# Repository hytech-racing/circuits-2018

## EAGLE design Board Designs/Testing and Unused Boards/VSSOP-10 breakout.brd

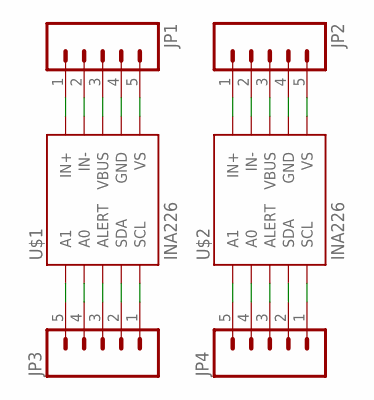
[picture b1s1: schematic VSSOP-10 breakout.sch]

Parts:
JP1, JP2, JP3, JP4: M05; 1X05
U$1, U$2: INA226; VSSOP-10

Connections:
unnamed: JP4.1, U$2.5 (SCL)
unnamed: JP4.2, U$2.4 (SDA)
unnamed: JP4.3, U$2.3 (ALERT)
unnamed: JP4.4, U$2.2 (A0)
unnamed: JP4.5, U$2.1 (A1)
unnamed: JP3.1, U$1.5 (SCL)
unnamed: JP3.2, U$1.4 (SDA)
unnamed: JP3.3, U$1.3 (ALERT)
unnamed: JP3.4, U$1.2 (A0)
unnamed: JP3.5, U$1.1 (A1)
unnamed: JP2.1, U$2.10 (IN+)
unnamed: JP2.2, U$2.9 (IN-)
unnamed: JP2.3, U$2.8 (VBUS)
unnamed: JP2.4, U$2.7 (GND)
unnamed: JP2.5, U$2.6 (VS)
unnamed: JP1.1, U$1.10 (IN+)
unnamed: JP1.2, U$1.9 (IN-)
unnamed: JP1.3, U$1.8 (VBUS)
unnamed: JP1.4, U$1.7 (GND)
unnamed: JP1.5, U$1.6 (VS)

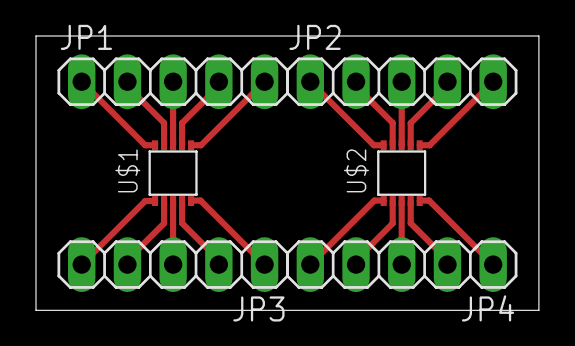
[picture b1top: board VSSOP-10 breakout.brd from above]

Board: 2 copper layers, 27.9 x 15.2 mm, 6 parts (0 on the bottom side), 20 nets.

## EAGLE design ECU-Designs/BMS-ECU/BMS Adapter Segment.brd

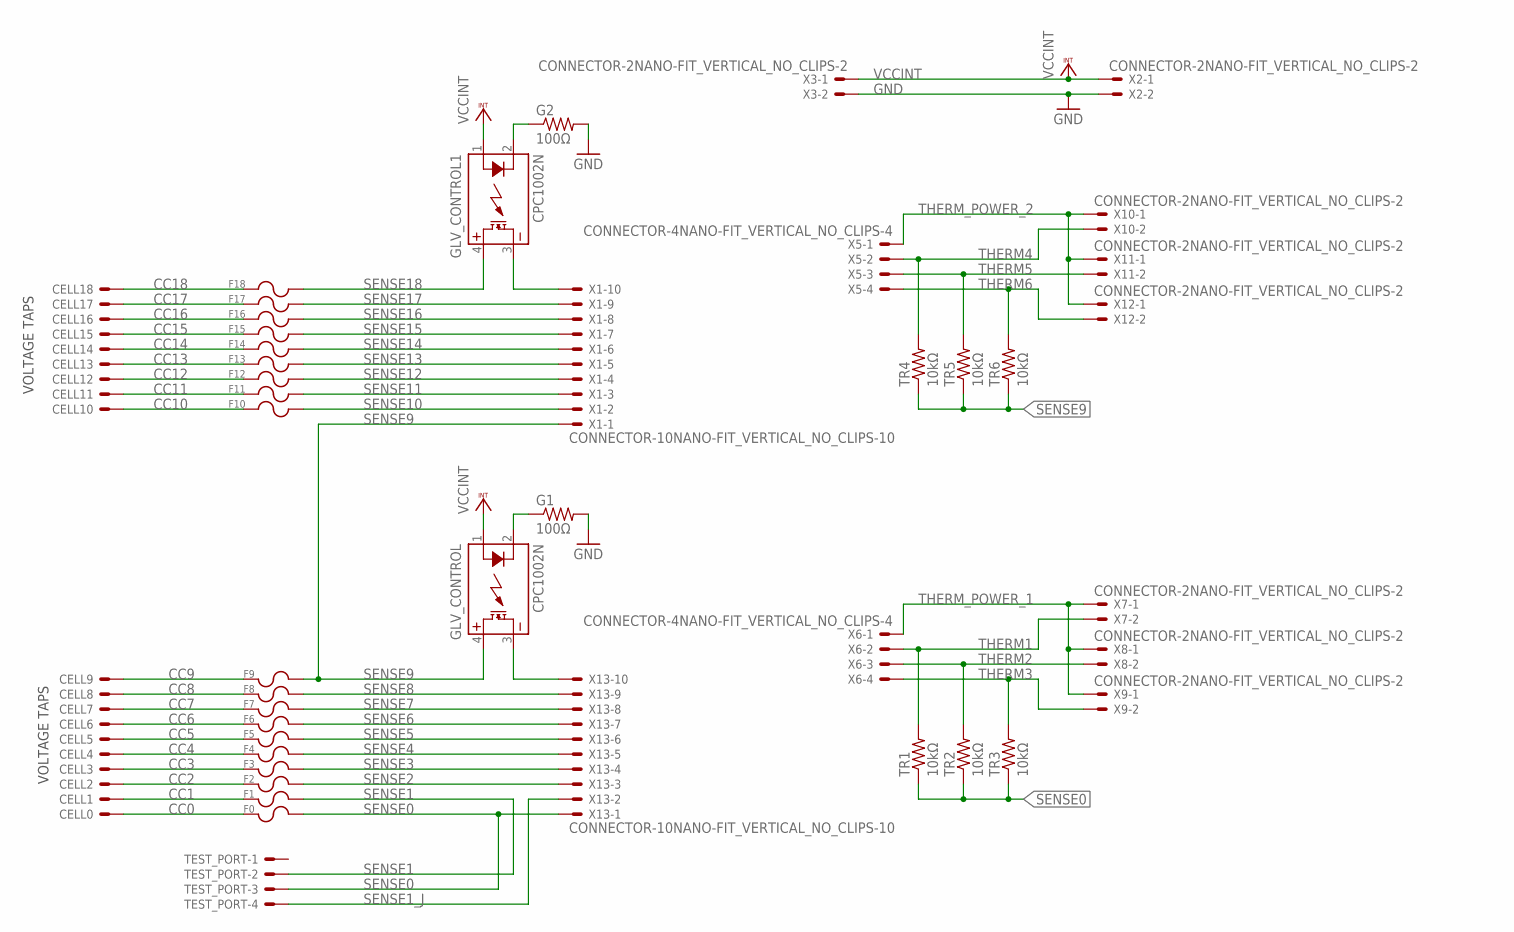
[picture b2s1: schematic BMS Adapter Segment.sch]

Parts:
CELL0, CELL1, CELL2, CELL3, CELL4, CELL5, CELL6, CELL7, CELL8, CELL9, CELL10, CELL11, CELL12, CELL13, CELL14, CELL15, CELL16, CELL17, CELL18: BATTERY_SPRING_KEYSTONE5222; KEYSTONE5222
F0, F1, F2, F3, F4, F5, F6, F7, F8, F9, F10, F11, F12, F13, F14, F15, F16, F17, F18: 0751.0110_FUSE_CLIP; 0751.0110
G1, G2: 100Ω; 0805
GLV_CONTROL, GLV_CONTROL1: CPC1002N; SOP04
TEST_PORT: MINIFIT_5566-4
TR1, TR2, TR3, TR4, TR5, TR6: 10kΩ; 0805
X1, X13: CONNECTOR-10NANO-FIT_VERTICAL_NO_CLIPS-10; NANO-FIT_VERTICAL_NO_CLIPS-10
X2, X3, X7, X8, X9, X10, X11, X12: CONNECTOR-2NANO-FIT_VERTICAL_NO_CLIPS-2; NANO-FIT_VERTICAL_NO_CLIPS-2
X5, X6: CONNECTOR-4NANO-FIT_VERTICAL_NO_CLIPS-4; NANO-FIT_VERTICAL_NO_CLIPS-4

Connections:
CC0: CELL0.P$1, F0.L1 (1), F0.L2 (1)
CC1: CELL1.P$1, F1.L1 (1), F1.L2 (1)
CC2: CELL2.P$1, F2.L1 (1), F2.L2 (1)
CC3: CELL3.P$1, F3.L1 (1), F3.L2 (1)
CC4: CELL4.P$1, F4.L1 (1), F4.L2 (1)
CC5: CELL5.P$1, F5.L1 (1), F5.L2 (1)
CC6: CELL6.P$1, F6.L1 (1), F6.L2 (1)
CC7: CELL7.P$1, F7.L1 (1), F7.L2 (1)
CC8: CELL8.P$1, F8.L1 (1), F8.L2 (1)
CC9: CELL9.P$1, F9.L1 (1), F9.L2 (1)
CC10: CELL10.P$1, F10.L1 (1), F10.L2 (1)
CC11: CELL11.P$1, F11.L1 (1), F11.L2 (1)
CC12: CELL12.P$1, F12.L1 (1), F12.L2 (1)
CC13: CELL13.P$1, F13.L1 (1), F13.L2 (1)
CC14: CELL14.P$1, F14.L1 (1), F14.L2 (1)
CC15: CELL15.P$1, F15.L1 (1), F15.L2 (1)
CC16: CELL16.P$1, F16.L1 (1), F16.L2 (1)
CC17: CELL17.P$1, F17.L1 (1), F17.L2 (1)
CC18: CELL18.P$1, F18.L1 (1), F18.L2 (1)
GND: G1.2, G2.2, X2.P$2, X3.P$2
unnamed: GLV_CONTROL1.3 (DC-), X1.P$10
unnamed: GLV_CONTROL.3 (DC-), X13.P$10
SENSE0: F0.R1 (2), F0.R2 (2), TEST_PORT.3, TR1.1, TR2.1, TR3.1, X13.P$1
SENSE1: F1.R1 (2), F1.R2 (2), TEST_PORT.2
SENSE1_J: TEST_PORT.4, X13.P$2
SENSE2: F2.R1 (2), F2.R2 (2), X13.P$3
SENSE3: F3.R1 (2), F3.R2 (2), X13.P$4
SENSE4: F4.R1 (2), F4.R2 (2), X13.P$5
SENSE5: F5.R1 (2), F5.R2 (2), X13.P$6
SENSE6: F6.R1 (2), F6.R2 (2), X13.P$7
SENSE7: F7.R1 (2), F7.R2 (2), X13.P$8
SENSE8: F8.R1 (2), F8.R2 (2), X13.P$9
SENSE9: F9.R1 (2), F9.R2 (2), GLV_CONTROL.4 (DC+), TR4.1, TR5.1, TR6.1, X1.P$1
SENSE10: F10.R1 (2), F10.R2 (2), X1.P$2
SENSE11: F11.R1 (2), F11.R2 (2), X1.P$3
SENSE12: F12.R1 (2), F12.R2 (2), X1.P$4
SENSE13: F13.R1 (2), F13.R2 (2), X1.P$5
SENSE14: F14.R1 (2), F14.R2 (2), X1.P$6
SENSE15: F15.R1 (2), F15.R2 (2), X1.P$7
SENSE16: F16.R1 (2), F16.R2 (2), X1.P$8
SENSE17: F17.R1 (2), F17.R2 (2), X1.P$9
SENSE18: F18.R1 (2), F18.R2 (2), GLV_CONTROL1.4 (DC+)
SSR-: G1.1, GLV_CONTROL.2 (CONTROL-)
SSR-1: G2.1, GLV_CONTROL1.2 (CONTROL-)
THERM1: TR1.2, X6.P$2, X7.P$2
THERM2: TR2.2, X6.P$3, X8.P$2
THERM3: TR3.2, X6.P$4, X9.P$2
THERM4: TR4.2, X5.P$2, X10.P$2
THERM5: TR5.2, X5.P$3, X11.P$2
THERM6: TR6.2, X5.P$4, X12.P$2
THERM_POWER_1: X6.P$1, X7.P$1, X8.P$1, X9.P$1
THERM_POWER_2: X5.P$1, X10.P$1, X11.P$1, X12.P$1
VCCINT: GLV_CONTROL.1 (CONTROL+), GLV_CONTROL1.1 (CONTROL+), X2.P$1, X3.P$1

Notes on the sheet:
VOLTAGE TAPS

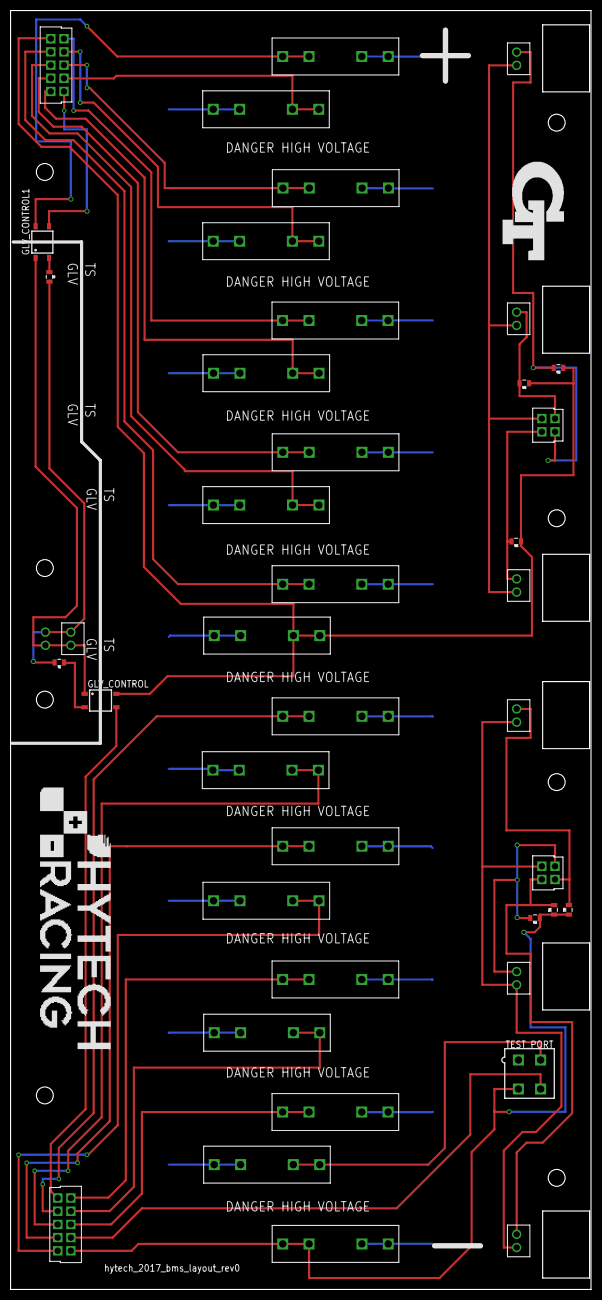
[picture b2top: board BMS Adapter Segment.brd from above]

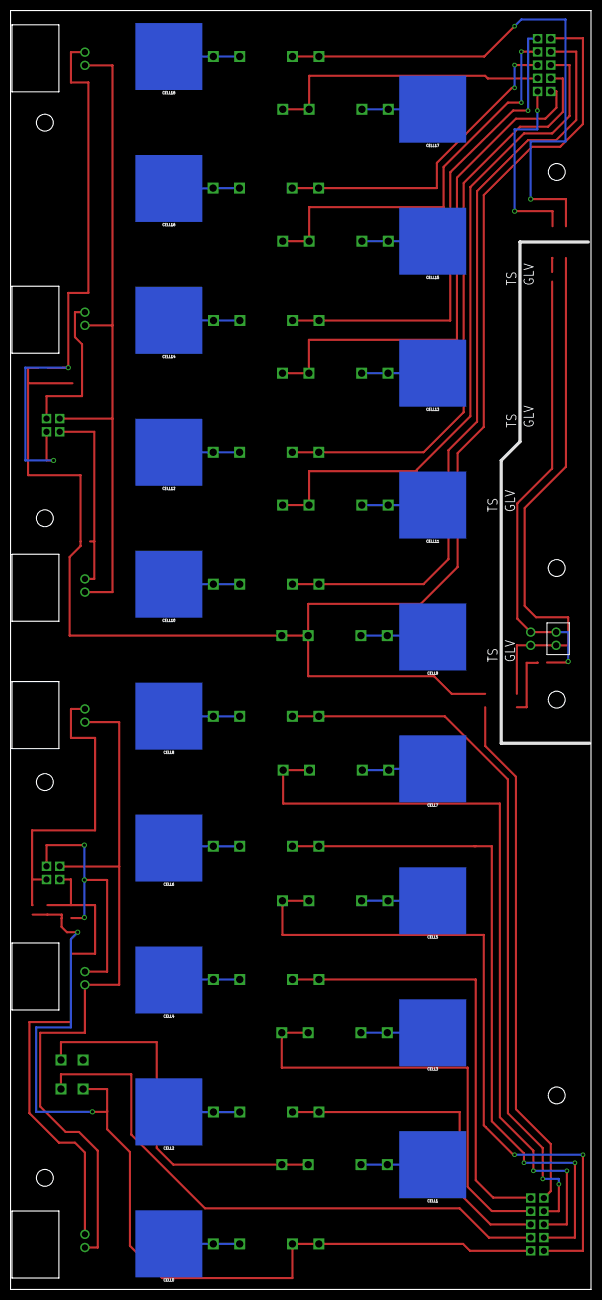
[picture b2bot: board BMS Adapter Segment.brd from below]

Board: 2 copper layers, 110.0 x 242.4 mm, 61 parts (20 on the bottom side), 53 nets.

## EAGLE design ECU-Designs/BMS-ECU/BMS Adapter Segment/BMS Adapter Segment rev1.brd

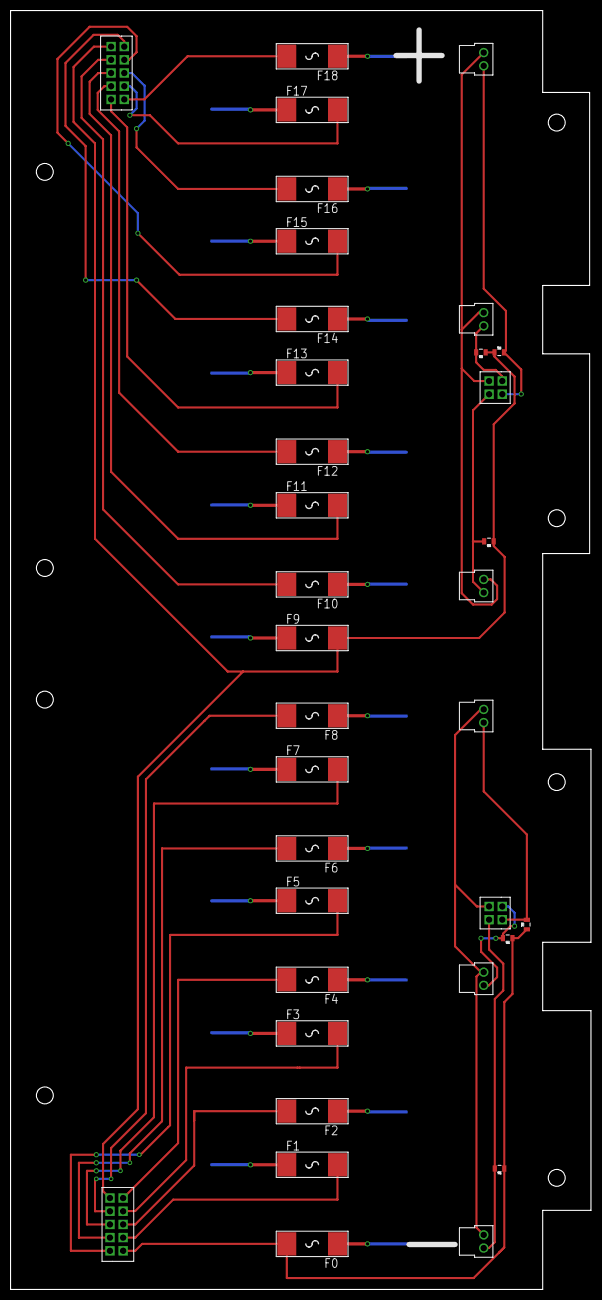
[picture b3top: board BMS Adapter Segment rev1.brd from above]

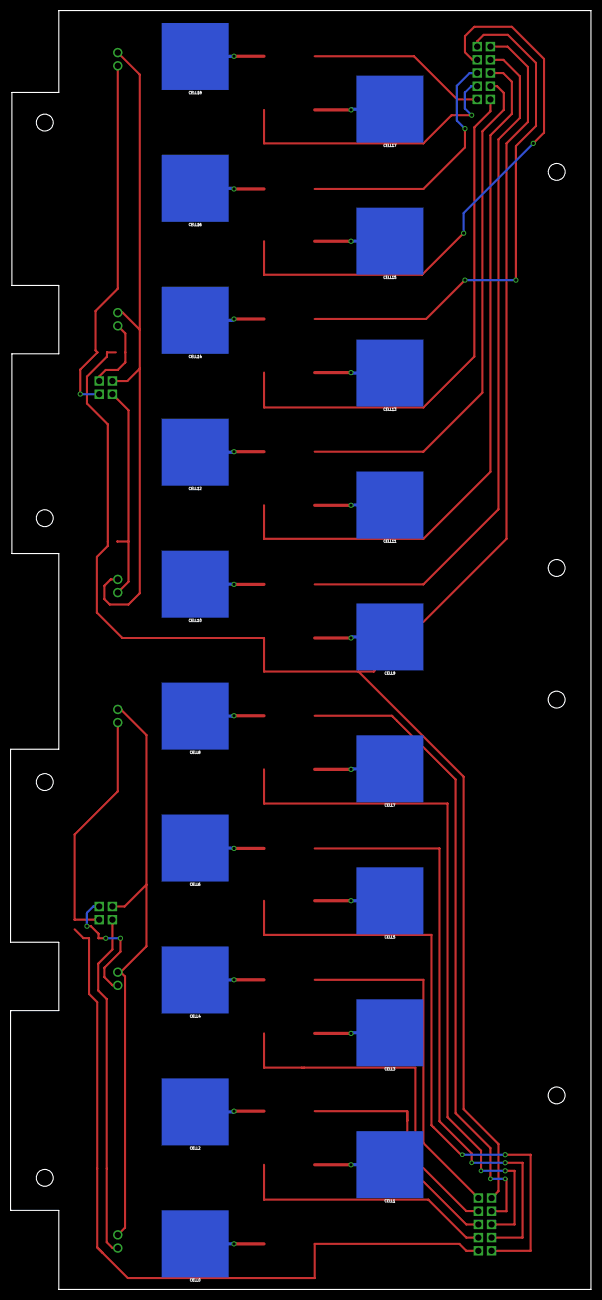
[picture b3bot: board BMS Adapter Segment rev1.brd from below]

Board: 2 copper layers, 110.0 x 242.3 mm, 54 parts (19 on the bottom side), 46 nets.

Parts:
CELL0, CELL1, CELL2, CELL3, CELL4, CELL5, CELL6, CELL7, CELL8, CELL9, CELL10, CELL11, CELL12, CELL13, CELL14, CELL15, CELL16, CELL17, CELL18: KEYSTONE5222
F0, F1, F2, F3, F4, F5, F6, F7, F8, F9, F10, F11, F12, F13, F14, F15, F16, F17, F18: OMF_250
TR1, TR2, TR3, TR4, TR5, TR6: 10kΩ; 0805
X1, X13: CONNECTOR-10NANO-FIT_VERTICAL-10; NANO-FIT_VERTICAL-10
X5, X6: CONNECTOR-4NANO-FIT-VERTICAL-4; NANO-FIT_VERTICAL-4
X7, X8, X9, X10, X11, X12: CONNECTOR-2NANO-FIT_VERTICAL-2; NANO-FIT_VERTICAL-2

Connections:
CC0: CELL0.P$1, F0.P$1
CC1: CELL1.P$1, F1.P$1
CC2: CELL2.P$1, F2.P$1
CC3: CELL3.P$1, F3.P$1
CC4: CELL4.P$1, F4.P$1
CC5: CELL5.P$1, F5.P$1
CC6: CELL6.P$1, F6.P$1
CC7: CELL7.P$1, F7.P$1
CC8: CELL8.P$1, F8.P$1
CC9: CELL9.P$1, F9.P$1
CC10: CELL10.P$1, F10.P$1
CC11: CELL11.P$1, F11.P$1
CC12: CELL12.P$1, F12.P$1
CC13: CELL13.P$1, F13.P$1
CC14: CELL14.P$1, F14.P$1
CC15: CELL15.P$1, F15.P$1
CC16: CELL16.P$1, F16.P$1
CC17: CELL17.P$1, F17.P$1
CC18: CELL18.P$1, F18.P$1
SENSE0: F0.P$2, TR1.1, TR2.1, TR3.1, X13.P$1
SENSE1: F1.P$2, X13.P$2
SENSE2: F2.P$2, X13.P$3
SENSE3: F3.P$2, X13.P$4
SENSE4: F4.P$2, X13.P$5
SENSE5: F5.P$2, X13.P$6
SENSE6: F6.P$2, X13.P$7
SENSE7: F7.P$2, X13.P$8
SENSE8: F8.P$2, X13.P$9
SENSE9: F9.P$2, TR4.1, TR5.1, TR6.1, X1.P$1, X13.P$10
SENSE10: F10.P$2, X1.P$2
SENSE11: F11.P$2, X1.P$3
SENSE12: F12.P$2, X1.P$4
SENSE13: F13.P$2, X1.P$5
SENSE14: F14.P$2, X1.P$6
SENSE15: F15.P$2, X1.P$7
SENSE16: F16.P$2, X1.P$8
SENSE17: F17.P$2, X1.P$9
SENSE18: F18.P$2, X1.P$10
THERM1: TR1.2, X6.P$2, X7.P$2
THERM2: TR2.2, X6.P$3, X8.P$2
THERM3: TR3.2, X6.P$4, X9.P$2
THERM4: TR4.2, X5.P$2, X10.P$2
THERM5: TR5.2, X5.P$3, X11.P$2
THERM6: TR6.2, X5.P$4, X12.P$2
THERM_POWER_1: X6.P$1, X7.P$1, X8.P$1, X9.P$1
THERM_POWER_2: X5.P$1, X10.P$1, X11.P$1, X12.P$1

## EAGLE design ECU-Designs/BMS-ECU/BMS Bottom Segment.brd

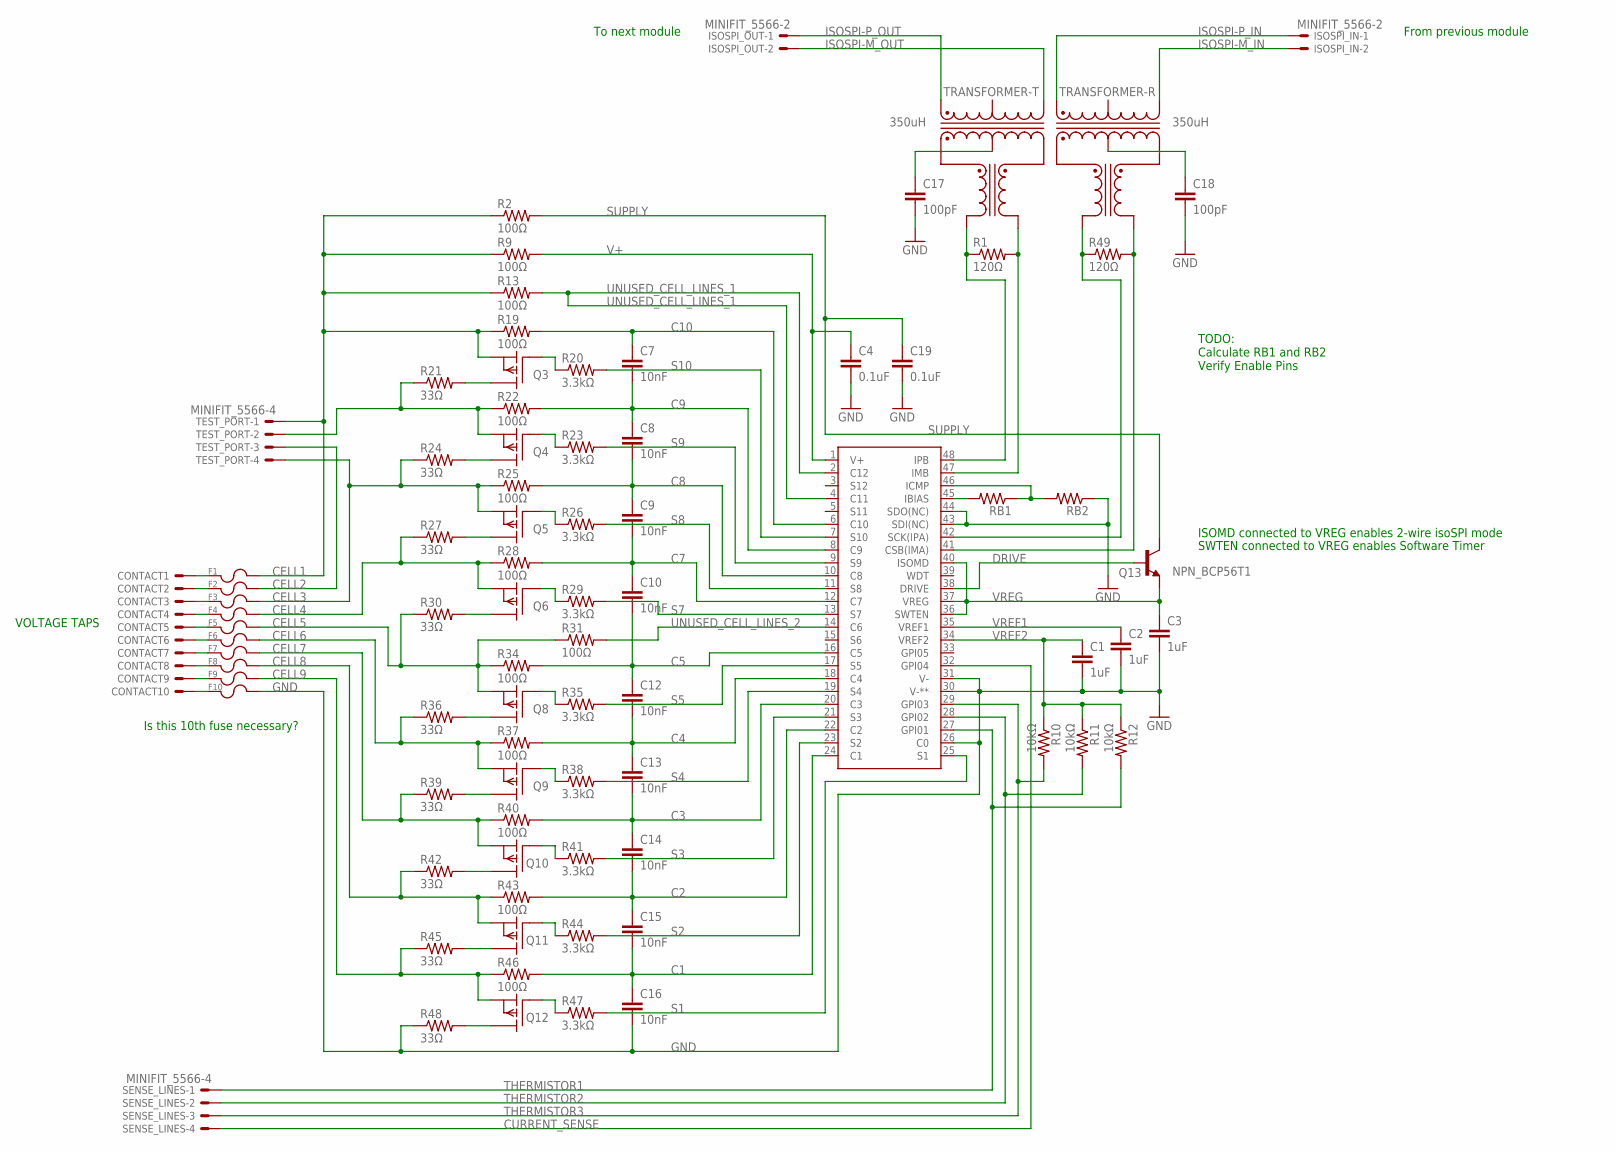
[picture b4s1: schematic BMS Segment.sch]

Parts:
C1, C2, C3: 1uF; 0805
C4, C19: 0.1uF; 0805
C7, C8, C9, C10, C12, C13, C14, C15, C16: 10nF; 0805
C17, C18: 100pF; 0805
CONTACT1, CONTACT2, CONTACT3, CONTACT4, CONTACT5, CONTACT6, CONTACT7, CONTACT8, CONTACT9, CONTACT10: SPRING_CONTACT; S1791-42R
F1, F2, F3, F4, F5, F6, F7, F8, F9, F10: 0751.0110_FUSE_CLIP; 0751.0110
ISOSPI_IN: MINIFIT_5566-2
ISOSPI_OUT: MINIFIT_5566-2
Q3, Q4, Q5, Q6, Q8, Q9, Q10, Q11, Q12: P-CHANNEL_MOSFET_DMP3099L-7; SOT23
Q13: NPN_BCP56T1; SOT223
R1, R49: 120Ω; 0805
R2, R9, R13, R19, R22, R25, R28, R31, R34, R37, R40, R43, R46: 100Ω; 0805
R10, R11, R12: 10kΩ; 0805
R20, R23, R26, R29, R35, R38, R41, R44, R47: 3.3kΩ; 0805
R21, R24, R27, R30, R36, R39, R42, R45, R48: 33Ω; R2512
RB1, RB2: RESISTOR0805-RES; 0805
SENSE_LINES: MINIFIT_5566-4
TEST_PORT: MINIFIT_5566-4
TRANSFORMER-: 350uH; 749010013
U$2: LTC6804-1; LTC6804

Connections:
C1: C15.2, C16.1, R46.2, U$2.24 (C1)
C2: C14.2, C15.1, R43.2, U$2.22 (C2)
C3: C13.2, C14.1, R40.2, U$2.20 (C3)
C4: C12.2, C13.1, R37.2, U$2.18 (C4)
C5: C10.2, C12.1, R34.2, U$2.16 (C5)
C7: C9.2, C10.1, R28.2, U$2.12 (C7)
C8: C8.2, C9.1, R25.2, U$2.10 (C8)
C9: C7.2, C8.1, R22.2, U$2.8 (C9)
C10: C7.1, R19.2, U$2.6 (C10)
CELL1: F1.R1 (2), F1.R2 (2), Q3.2 (S), R2.1, R9.1, R13.1, R19.1, TEST_PORT.1
CELL2: F2.R1 (2), F2.R2 (2), Q4.2 (S), R21.1, R22.1, TEST_PORT.2, TEST_PORT.3
CELL3: F3.R1 (2), F3.R2 (2), Q5.2 (S), R24.1, R25.1, TEST_PORT.4
CELL4: F4.R1 (2), F4.R2 (2), Q6.2 (S), R27.1, R28.1
CELL5: F5.R1 (2), F5.R2 (2), Q8.2 (S), R30.1, R31.1, R34.1
CELL6: F6.R1 (2), F6.R2 (2), Q9.2 (S), R36.1, R37.1
CELL7: F7.R1 (2), F7.R2 (2), Q10.2 (S), R39.1, R40.1
CELL8: F8.R1 (2), F8.R2 (2), Q11.2 (S), R42.1, R43.1
CELL9: F9.R1 (2), F9.R2 (2), Q12.2 (S), R45.1, R46.1
CURRENT_SENSE: SENSE_LINES.4, U$2.32 (GPI04)
DRIVE: Q13.1 (BASE), U$2.38 (DRIVE)
GND: C1.2, C2.2, C3.2, C4.2, C16.2, C17.2, C18.2, C19.2, F10.R1 (2), F10.R2 (2), R48.1, RB2.1, U$2.26 (C0), U$2.30 (V-**), U$2.31 (V-), U$2.43 (SDI(NC)), U$2.44 (SDO(NC))
unnamed: C18.1, TRANSFORMER-.10 (CX)
unnamed: C17.1, TRANSFORMER-.15 (CX)
unnamed: RB1.2, U$2.45 (IBIAS)
unnamed: R1.1, TRANSFORMER-.16 (X+), U$2.48 (IPB)
unnamed: RB1.1, RB2.2, U$2.46 (ICMP)
unnamed: R49.1, TRANSFORMER-.11 (X+), U$2.42 (SCK(IPA))
unnamed: R49.2, TRANSFORMER-.9 (X-), U$2.41 (CSB(IMA))
unnamed: CONTACT1.P$1, F1.L1 (1), F1.L2 (1)
unnamed: Q3.1 (G), R20.1
unnamed: CONTACT2.P$1, F2.L1 (1), F2.L2 (1)
unnamed: CONTACT3.P$1, F3.L1 (1), F3.L2 (1)
unnamed: Q3.3 (D), R21.2
unnamed: CONTACT4.P$1, F4.L1 (1), F4.L2 (1)
unnamed: Q8.1 (G), R35.1
unnamed: Q9.1 (G), R38.1
unnamed: CONTACT5.P$1, F5.L1 (1), F5.L2 (1)
unnamed: CONTACT6.P$1, F6.L1 (1), F6.L2 (1)
unnamed: Q4.3 (D), R24.2
unnamed: CONTACT7.P$1, F7.L1 (1), F7.L2 (1)
unnamed: Q10.1 (G), R41.1
unnamed: Q11.1 (G), R44.1
unnamed: Q12.1 (G), R47.1
unnamed: Q5.3 (D), R27.2
unnamed: CONTACT8.P$1, F8.L1 (1), F8.L2 (1)
unnamed: CONTACT9.P$1, F9.L1 (1), F9.L2 (1)
unnamed: CONTACT10.P$1, F10.L1 (1), F10.L2 (1)
unnamed: Q6.3 (D), R30.2
unnamed: R1.2, TRANSFORMER-.14 (X-), U$2.47 (IMB)
unnamed: Q8.3 (D), R36.2
unnamed: Q9.3 (D), R39.2
unnamed: Q10.3 (D), R42.2
unnamed: Q11.3 (D), R45.2
unnamed: Q12.3 (D), R48.2
unnamed: Q4.1 (G), R23.1
unnamed: Q5.1 (G), R26.1
unnamed: Q6.1 (G), R29.1
S1: R47.2, U$2.25 (S1)
S2: R44.2, U$2.23 (S2)
S3: R41.2, U$2.21 (S3)
S4: R38.2, U$2.19 (S4)
S5: R35.2, U$2.17 (S5)
S7: R29.2, U$2.13 (S7)
S8: R26.2, U$2.11 (S8)
S9: R23.2, U$2.9 (S9)
S10: R20.2, U$2.7 (S10)
SUPPLY: C19.1, Q13.2 (COLLECTOR), Q13.4 (COLLECTOR), R2.2
THERMISTOR1: R12.2, SENSE_LINES.1, U$2.27 (GPI01)
THERMISTOR2: R11.2, SENSE_LINES.2, U$2.28 (GPI02)
THERMISTOR3: R10.2, SENSE_LINES.3, U$2.29 (GPI03)
UNUSED_CELL_LINES_1: R13.2, U$2.2 (C12), U$2.4 (C11)
UNUSED_CELL_LINES_2: R31.2, U$2.14 (C6)
V+: C4.1, R9.2, U$2.1 (V+)
VREF1: C2.1, U$2.35 (VREF1)
VREF2: C1.1, R10.1, R11.1, R12.1, U$2.34 (VREF2)
VREG: C3.1, Q13.3 (EMITTER), U$2.36 (SWTEN), U$2.37 (VREG), U$2.40 (ISOMD)

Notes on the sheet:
SWTEN connected to VREG enables Software Timer
ISOMD connected to VREG enables 2-wire isoSPI mode
VOLTAGE TAPS
To next module
From previous module
TODO: Calculate RB1 and RB2 Verify Enable Pins
Is this 10th fuse necessary?

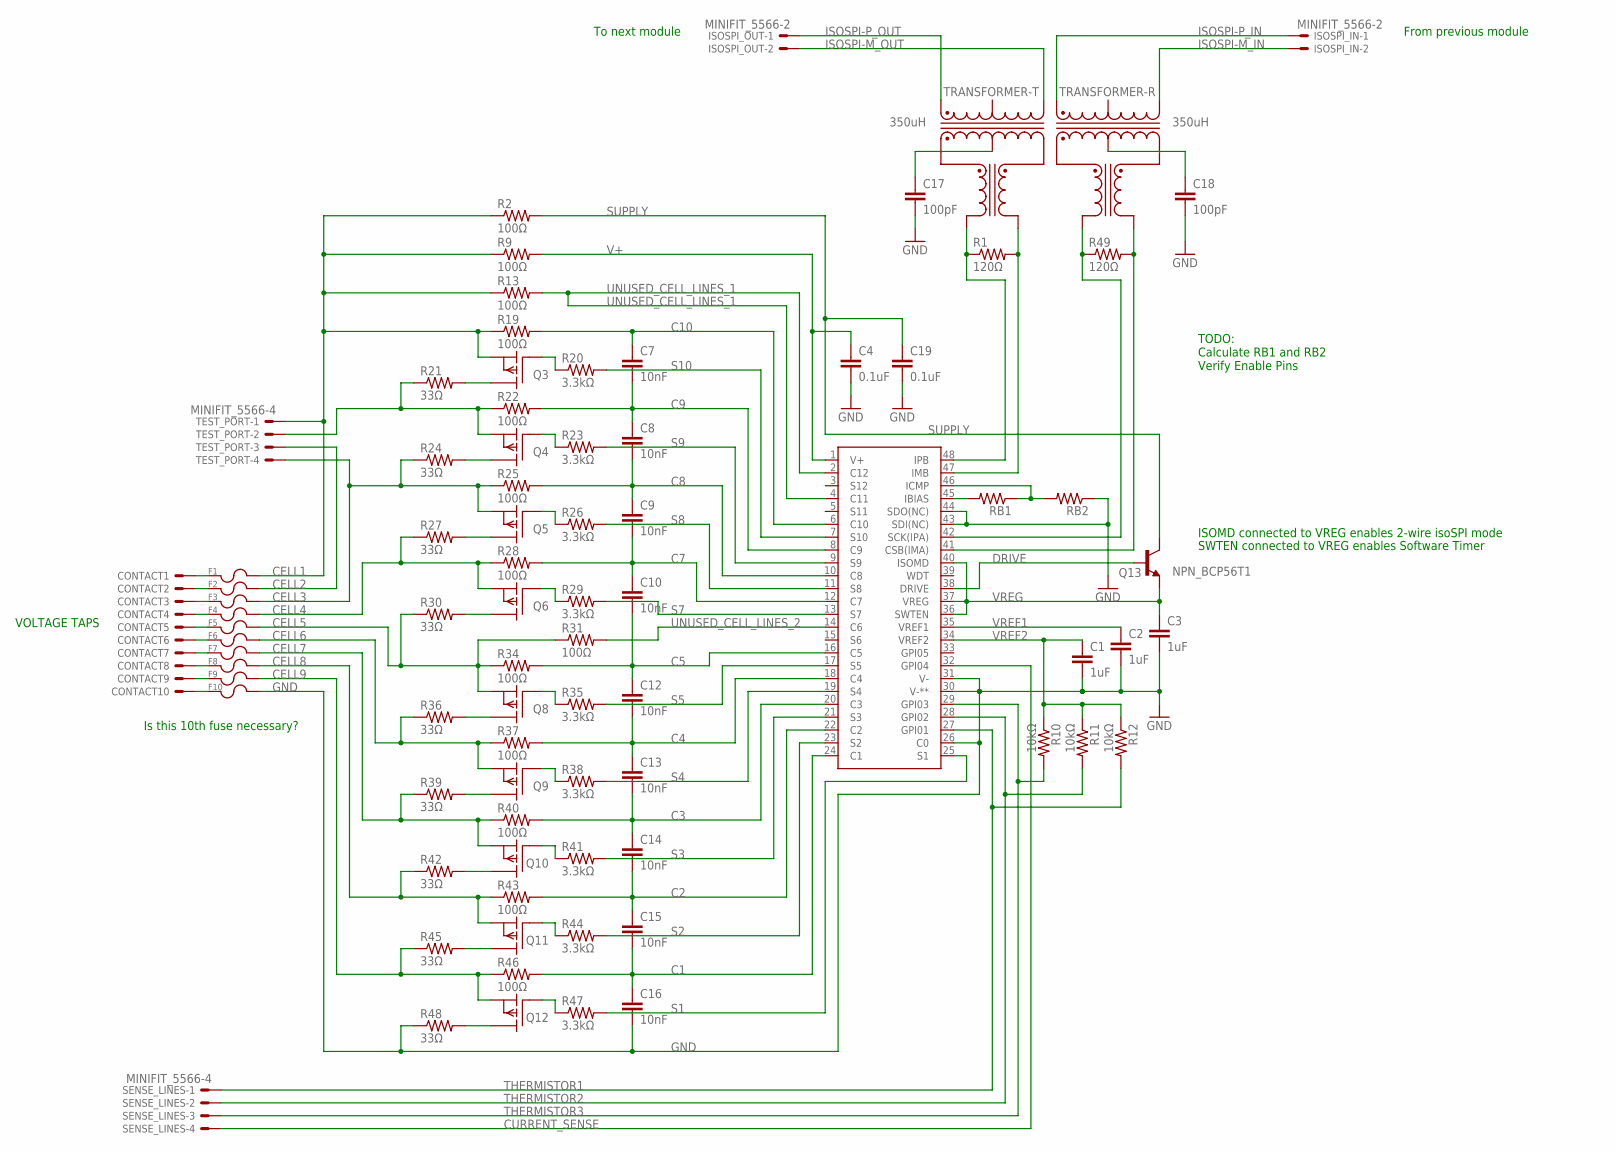
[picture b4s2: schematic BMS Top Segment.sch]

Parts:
C1, C2, C3: 1uF; 0805
C4, C19: 0.1uF; 0805
C7, C8, C9, C10, C12, C13, C14, C15, C16: 10nF; 0805
C17, C18: 100pF; 0805
CONTACT1, CONTACT2, CONTACT3, CONTACT4, CONTACT5, CONTACT6, CONTACT7, CONTACT8, CONTACT9, CONTACT10: SPRING_CONTACT; S1791-42R
F1, F2, F3, F4, F5, F6, F7, F8, F9, F10: 0751.0110_FUSE_CLIP; 0751.0110
ISOSPI_IN: MINIFIT_5566-2
ISOSPI_OUT: MINIFIT_5566-2
Q3, Q4, Q5, Q6, Q8, Q9, Q10, Q11, Q12: P-CHANNEL_MOSFET_DMP3099L-7; SOT23
Q13: NPN_BCP56T1; SOT223
R1, R49: 120Ω; 0805
R2, R9, R13, R19, R22, R25, R28, R31, R34, R37, R40, R43, R46: 100Ω; 0805
R10, R11, R12: 10kΩ; 0805
R20, R23, R26, R29, R35, R38, R41, R44, R47: 3.3kΩ; 0805
R21, R24, R27, R30, R36, R39, R42, R45, R48: 33Ω; R2512
RB1, RB2: RESISTOR0805-RES; 0805
SENSE_LINES: MINIFIT_5566-4
TEST_PORT: MINIFIT_5566-4
TRANSFORMER-: 350uH; 749010013
U$2: LTC6804-1; LTC6804

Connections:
C1: C15.2, C16.1, R46.2, U$2.24 (C1)
C2: C14.2, C15.1, R43.2, U$2.22 (C2)
C3: C13.2, C14.1, R40.2, U$2.20 (C3)
C4: C12.2, C13.1, R37.2, U$2.18 (C4)
C5: C10.2, C12.1, R34.2, U$2.16 (C5)
C7: C9.2, C10.1, R28.2, U$2.12 (C7)
C8: C8.2, C9.1, R25.2, U$2.10 (C8)
C9: C7.2, C8.1, R22.2, U$2.8 (C9)
C10: C7.1, R19.2, U$2.6 (C10)
CELL1: F1.R1 (2), F1.R2 (2), Q3.2 (S), R2.1, R9.1, R13.1, R19.1, TEST_PORT.1
CELL2: F2.R1 (2), F2.R2 (2), Q4.2 (S), R21.1, R22.1, TEST_PORT.2, TEST_PORT.3
CELL3: F3.R1 (2), F3.R2 (2), Q5.2 (S), R24.1, R25.1, TEST_PORT.4
CELL4: F4.R1 (2), F4.R2 (2), Q6.2 (S), R27.1, R28.1
CELL5: F5.R1 (2), F5.R2 (2), Q8.2 (S), R30.1, R31.1, R34.1
CELL6: F6.R1 (2), F6.R2 (2), Q9.2 (S), R36.1, R37.1
CELL7: F7.R1 (2), F7.R2 (2), Q10.2 (S), R39.1, R40.1
CELL8: F8.R1 (2), F8.R2 (2), Q11.2 (S), R42.1, R43.1
CELL9: F9.R1 (2), F9.R2 (2), Q12.2 (S), R45.1, R46.1
CURRENT_SENSE: SENSE_LINES.4, U$2.32 (GPI04)
DRIVE: Q13.1 (BASE), U$2.38 (DRIVE)
GND: C1.2, C2.2, C3.2, C4.2, C16.2, C17.2, C18.2, C19.2, F10.R1 (2), F10.R2 (2), R48.1, RB2.1, U$2.26 (C0), U$2.30 (V-**), U$2.31 (V-), U$2.43 (SDI(NC)), U$2.44 (SDO(NC))
unnamed: C18.1, TRANSFORMER-.10 (CX)
unnamed: C17.1, TRANSFORMER-.15 (CX)
unnamed: RB1.2, U$2.45 (IBIAS)
unnamed: R1.1, TRANSFORMER-.16 (X+), U$2.48 (IPB)
unnamed: RB1.1, RB2.2, U$2.46 (ICMP)
unnamed: R49.1, TRANSFORMER-.11 (X+), U$2.42 (SCK(IPA))
unnamed: R49.2, TRANSFORMER-.9 (X-), U$2.41 (CSB(IMA))
unnamed: CONTACT1.P$1, F1.L1 (1), F1.L2 (1)
unnamed: Q3.1 (G), R20.1
unnamed: CONTACT2.P$1, F2.L1 (1), F2.L2 (1)
unnamed: CONTACT3.P$1, F3.L1 (1), F3.L2 (1)
unnamed: Q3.3 (D), R21.2
unnamed: CONTACT4.P$1, F4.L1 (1), F4.L2 (1)
unnamed: Q8.1 (G), R35.1
unnamed: Q9.1 (G), R38.1
unnamed: CONTACT5.P$1, F5.L1 (1), F5.L2 (1)
unnamed: CONTACT6.P$1, F6.L1 (1), F6.L2 (1)
unnamed: Q4.3 (D), R24.2
unnamed: CONTACT7.P$1, F7.L1 (1), F7.L2 (1)
unnamed: Q10.1 (G), R41.1
unnamed: Q11.1 (G), R44.1
unnamed: Q12.1 (G), R47.1
unnamed: Q5.3 (D), R27.2
unnamed: CONTACT8.P$1, F8.L1 (1), F8.L2 (1)
unnamed: CONTACT9.P$1, F9.L1 (1), F9.L2 (1)
unnamed: CONTACT10.P$1, F10.L1 (1), F10.L2 (1)
unnamed: Q6.3 (D), R30.2
unnamed: R1.2, TRANSFORMER-.14 (X-), U$2.47 (IMB)
unnamed: Q8.3 (D), R36.2
unnamed: Q9.3 (D), R39.2
unnamed: Q10.3 (D), R42.2
unnamed: Q11.3 (D), R45.2
unnamed: Q12.3 (D), R48.2
unnamed: Q4.1 (G), R23.1
unnamed: Q5.1 (G), R26.1
unnamed: Q6.1 (G), R29.1
S1: R47.2, U$2.25 (S1)
S2: R44.2, U$2.23 (S2)
S3: R41.2, U$2.21 (S3)
S4: R38.2, U$2.19 (S4)
S5: R35.2, U$2.17 (S5)
S7: R29.2, U$2.13 (S7)
S8: R26.2, U$2.11 (S8)
S9: R23.2, U$2.9 (S9)
S10: R20.2, U$2.7 (S10)
SUPPLY: C19.1, Q13.2 (COLLECTOR), Q13.4 (COLLECTOR), R2.2
THERMISTOR1: R12.2, SENSE_LINES.1, U$2.27 (GPI01)
THERMISTOR2: R11.2, SENSE_LINES.2, U$2.28 (GPI02)
THERMISTOR3: R10.2, SENSE_LINES.3, U$2.29 (GPI03)
UNUSED_CELL_LINES_1: R13.2, U$2.2 (C12), U$2.4 (C11)
UNUSED_CELL_LINES_2: R31.2, U$2.14 (C6)
V+: C4.1, R9.2, U$2.1 (V+)
VREF1: C2.1, U$2.35 (VREF1)
VREF2: C1.1, R10.1, R11.1, R12.1, U$2.34 (VREF2)
VREG: C3.1, Q13.3 (EMITTER), U$2.36 (SWTEN), U$2.37 (VREG), U$2.40 (ISOMD)

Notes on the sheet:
SWTEN connected to VREG enables Software Timer
ISOMD connected to VREG enables 2-wire isoSPI mode
VOLTAGE TAPS
To next module
From previous module
TODO: Calculate RB1 and RB2 Verify Enable Pins
Is this 10th fuse necessary?

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
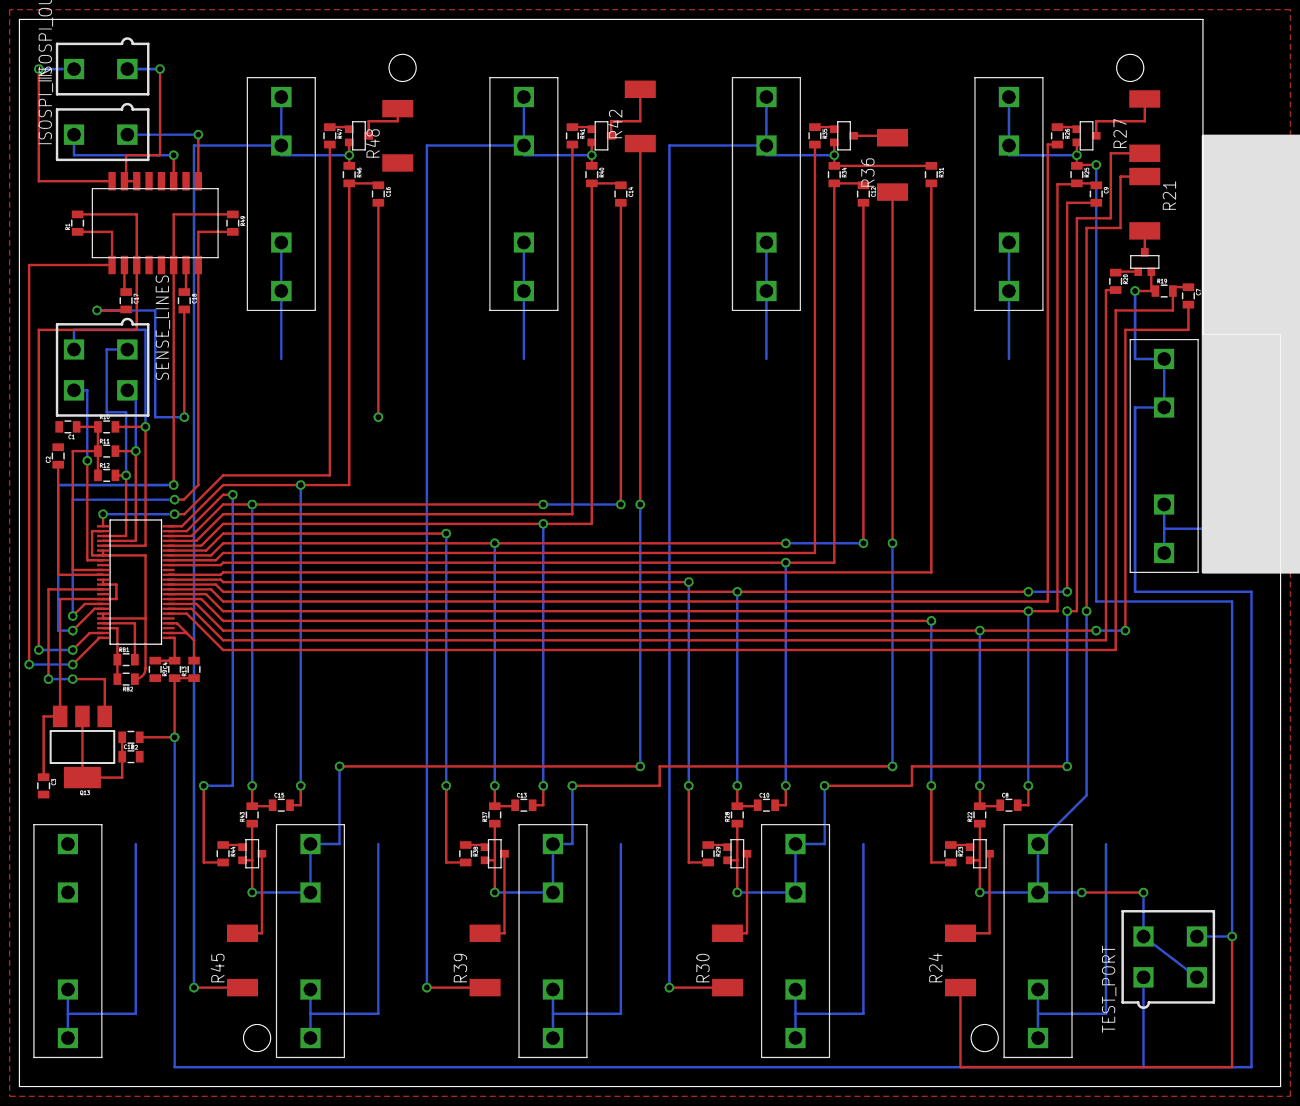
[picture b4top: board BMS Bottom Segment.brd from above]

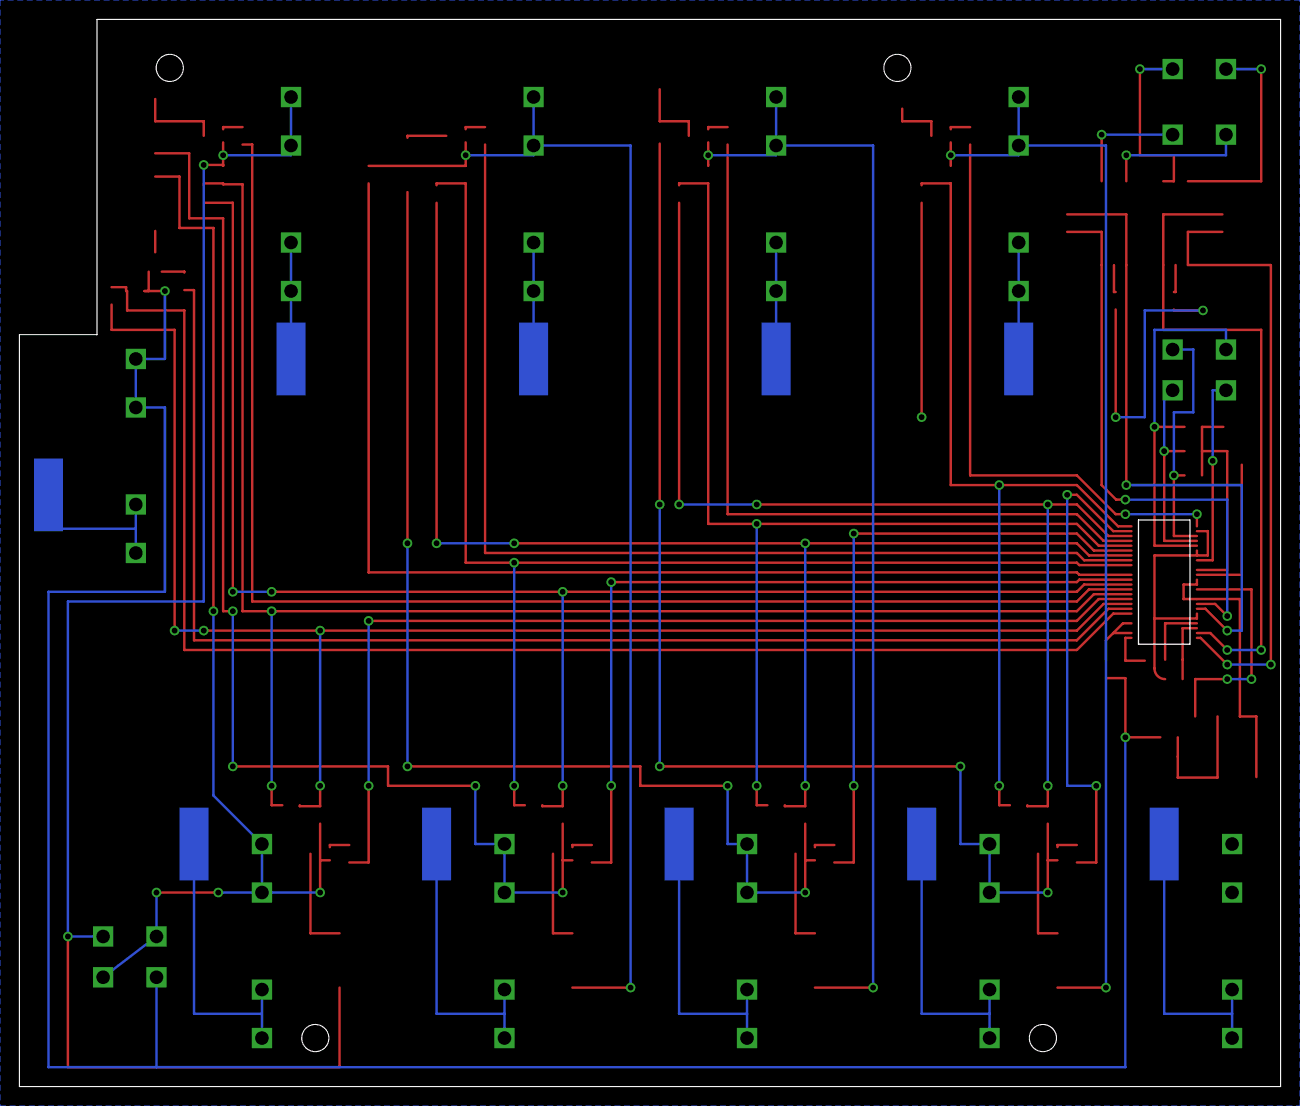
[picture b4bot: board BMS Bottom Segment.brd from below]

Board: 2 copper layers, 130.0 x 110.0 mm, 90 parts (10 on the bottom side), 80 nets.

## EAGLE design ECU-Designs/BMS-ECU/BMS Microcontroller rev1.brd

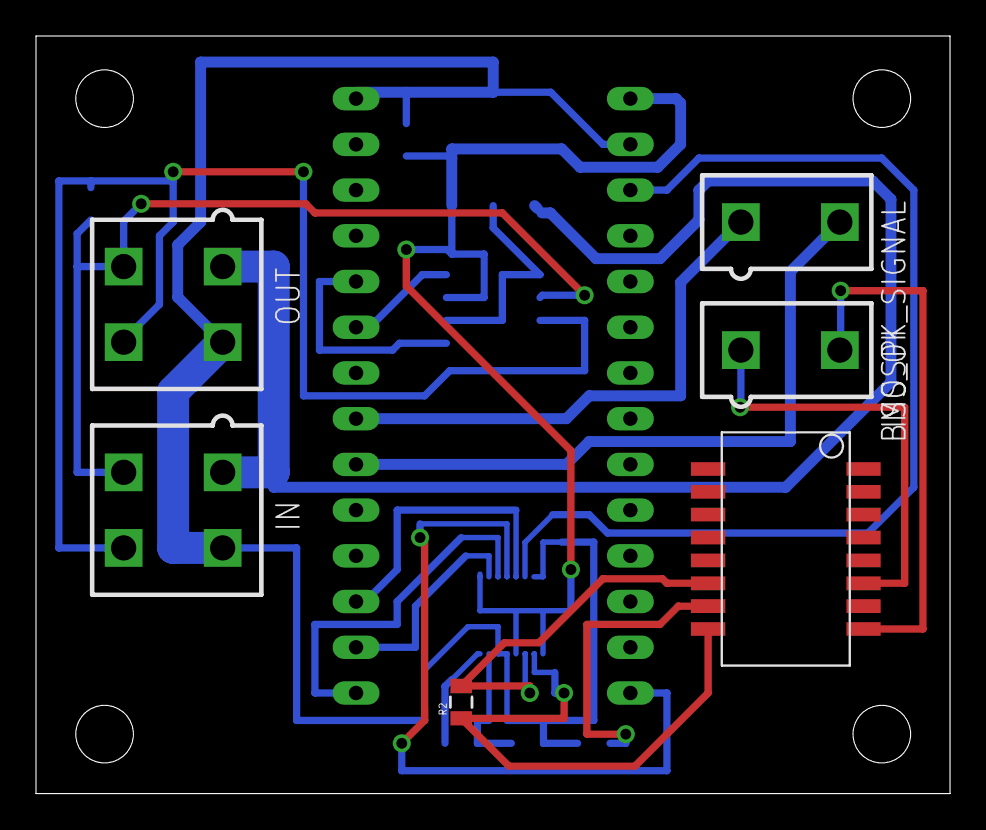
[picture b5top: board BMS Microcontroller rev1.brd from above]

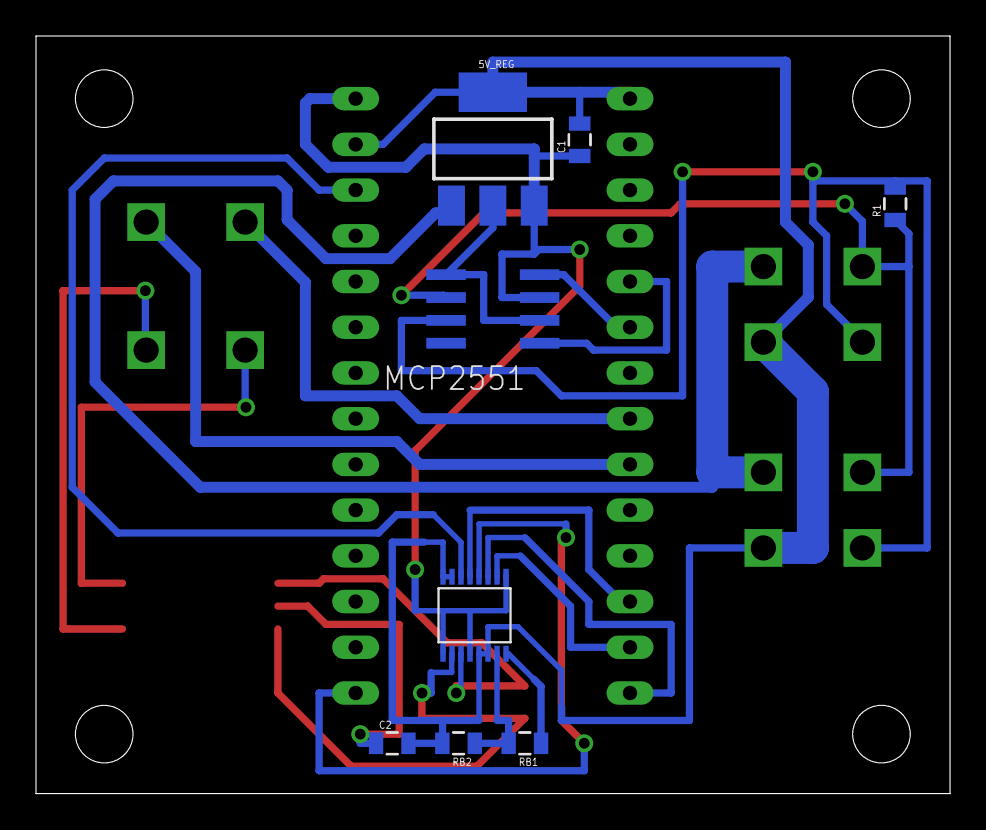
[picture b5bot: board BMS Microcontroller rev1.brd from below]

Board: 2 copper layers, 50.8 x 42.1 mm, 15 parts (8 on the bottom side), 21 nets.

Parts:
5V_REG: SOT223
BMS_OK_SIGNAL: MINIFIT_5566-2
C1: 0.1uF; 0805
C2: 100pF; 0805
IN: MINIFIT_5566-4
ISOSPI: MINIFIT_5566-2
MCP2551: MCP2551; SOIC-08
OUT: MINIFIT_5566-4
R1: 120Ω; 0805
R2: 120Ω; 0805
RB1, RB2: 0805
TRANSFORMER-: 749010013
U$1: LTC6820
U$3: TEENSY_3.2_SIMPLE

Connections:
5V_SUPPLY: 5V_REG.3, C1.1, MCP2551.3, U$1.1, U$1.9, U$1.12, U$3.VIN
12V_SUPPLY: 5V_REG.1, IN.1, OUT.1
CANH: IN.4, MCP2551.7, OUT.4, R1.2
CANL: IN.3, MCP2551.6, OUT.3, R1.1
CS: U$1.5, U$3.D10(TX2)
GND: 5V_REG.2, 5V_REG.4, C1.2, C2.2, IN.2, MCP2551.2, MCP2551.5, OUT.2, RB2.2, U$1.7, U$1.8, U$1.13, U$1.14, U$3.AGND, U$3.GND
ISOSPI-M: ISOSPI.2, TRANSFORMER-.8
ISOSPI-P: ISOSPI.1, TRANSFORMER-.6
MISO: U$1.3, U$3.D12
MOSI: U$1.2, U$3.D11
unnamed: U$1.6, U$3.3.3V
unnamed: U$1.4, U$3.D13
unnamed: C2.1, TRANSFORMER-.10
unnamed: RB1.1, U$1.16
unnamed: RB1.2, RB2.1, U$1.15
unnamed: R2.2, TRANSFORMER-.11, U$1.11
unnamed: R2.1, TRANSFORMER-.9, U$1.10
unnamed: BMS_OK_SIGNAL.1, U$3.D6
unnamed: BMS_OK_SIGNAL.2, U$3.D7(RX3)
RX: MCP2551.4, U$3.D4(CANRX)
TX: MCP2551.1, U$3.D3(CANTX)
